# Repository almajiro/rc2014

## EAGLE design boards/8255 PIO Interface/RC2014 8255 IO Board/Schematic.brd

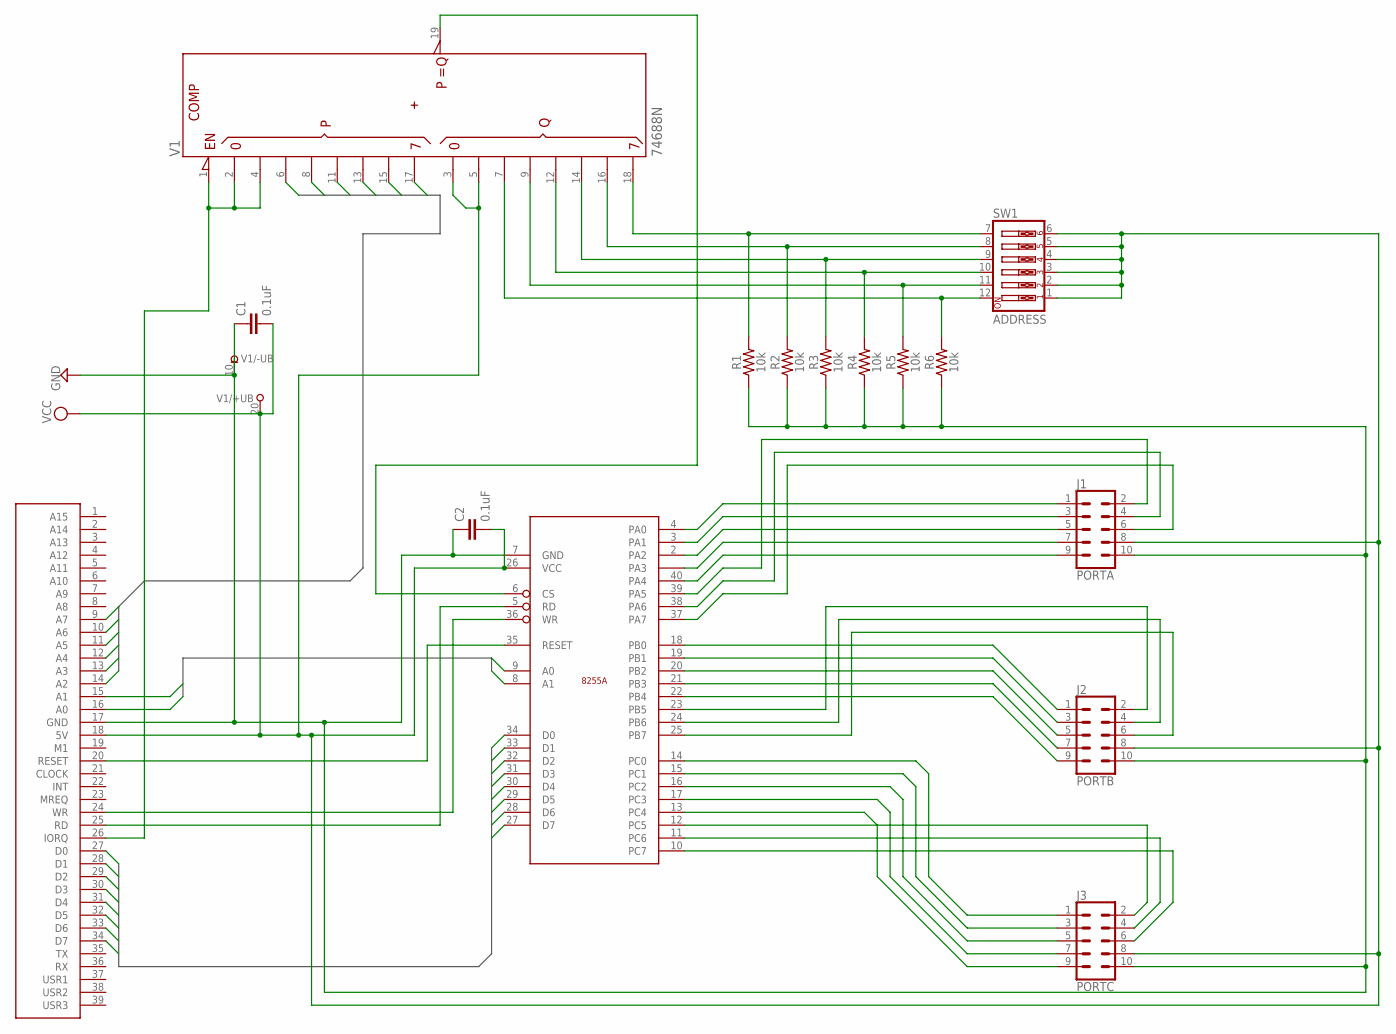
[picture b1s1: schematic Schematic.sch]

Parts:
C1, C2: 0.1uF; CAP-PTH-SMALL-KIT
J1: PORTA; 2X5-SHROUDED
J2: PORTB; 2X5-SHROUDED
J3: PORTC; 2X5-SHROUDED
R1, R2, R3, R4, R5, R6: 10k; AXIAL-0.3
SW1: ADDRESS; EDG-06
U$1: RC2014BUS
U$2: 8255
V1: 74688N; DIL20

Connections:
ADRBUS0: U$1.14 (A2), U$1.15 (A1), U$1.16 (A0), U$2.9 (A0), V1.6 (P2)
ADRBUS1: U$1.13 (A3), U$2.8 (A1), V1.8 (P3)
ADRBUS2: U$1.12 (A4), V1.11 (P4)
ADRBUS3: U$1.11 (A5), V1.13 (P5)
ADRBUS4: U$1.10 (A6), V1.15 (P6)
ADRBUS5: U$1.9 (A7), V1.17 (P7)
DATABUS0: U$1.27 (D0), U$2.34 (D0)
DATABUS1: U$1.28 (D1), U$2.33 (D1)
DATABUS2: U$1.29 (D2), U$2.32 (D2)
DATABUS3: U$1.30 (D3), U$2.31 (D3)
DATABUS4: U$1.31 (D4), U$2.30 (D4)
DATABUS5: U$1.32 (D5), U$2.29 (D5)
DATABUS6: U$1.33 (D6), U$2.28 (D6)
DATABUS7: U$1.34 (D7), U$2.27 (D7)
GND: C1.1, C2.1, J1.10, J2.10, J3.10, R1.P$1 (1), R2.P$1 (1), R3.P$1 (1), R4.P$1 (1), R5.P$1 (1), R6.P$1 (1), U$1.17 (GND), U$2.7 (GND), V1.10 (-UB)
unnamed: U$1.20 (RESET), U$2.35 (RESET)
unnamed: U$1.25 (RD), U$2.5 (RD)
unnamed: U$1.24 (WR), U$2.36 (WR)
unnamed: U$2.6 (CS), V1.19 (!P=Q)
unnamed: U$1.26 (IORQ), V1.1 (!G), V1.2 (P0), V1.4 (P1)
unnamed: R1.P$2 (2), SW1.7, V1.18 (Q7)
unnamed: R2.P$2 (2), SW1.8, V1.16 (Q6)
unnamed: R3.P$2 (2), SW1.9, V1.14 (Q5)
unnamed: R4.P$2 (2), SW1.10, V1.12 (Q4)
unnamed: R5.P$2 (2), SW1.11, V1.9 (Q3)
unnamed: R6.P$2 (2), SW1.12, V1.7 (Q2)
unnamed: J2.1, U$2.18 (PB0)
unnamed: J1.7, U$2.1 (PA3)
unnamed: J1.9, U$2.40 (PA4)
unnamed: J1.2, U$2.39 (PA5)
unnamed: J1.4, U$2.38 (PA6)
unnamed: J1.6, U$2.37 (PA7)
unnamed: J1.1, U$2.4 (PA0)
unnamed: J1.3, U$2.3 (PA1)
unnamed: J1.5, U$2.2 (PA2)
unnamed: J2.3, U$2.19 (PB1)
unnamed: J2.5, U$2.20 (PB2)
unnamed: J2.7, U$2.21 (PB3)
unnamed: J2.9, U$2.22 (PB4)
unnamed: J2.2, U$2.23 (PB5)
unnamed: J2.4, U$2.24 (PB6)
unnamed: J2.6, U$2.25 (PB7)
unnamed: J3.1, U$2.14 (PC0)
unnamed: J3.3, U$2.15 (PC1)
unnamed: J3.5, U$2.16 (PC2)
unnamed: J3.7, U$2.17 (PC3)
unnamed: J3.9, U$2.13 (PC4)
unnamed: J3.2, U$2.12 (PC5)
unnamed: J3.4, U$2.11 (PC6)
unnamed: J3.6, U$2.10 (PC7)
VCC: C1.2, C2.2, J1.8, J2.8, J3.8, SW1.1, SW1.2, SW1.3, SW1.4, SW1.5, SW1.6, U$1.18 (5V), U$2.26 (VCC), V1.3 (Q0), V1.5 (Q1), V1.20 (+UB)

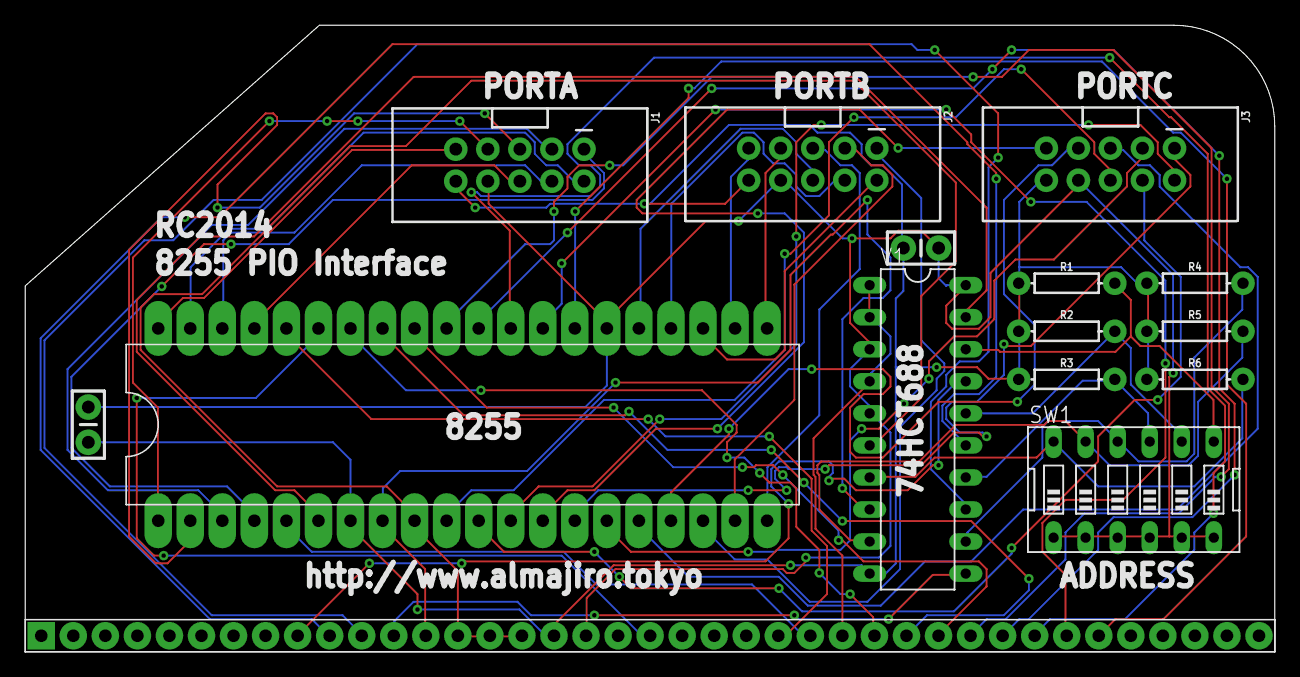
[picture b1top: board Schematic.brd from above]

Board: 2 copper layers, 99.0 x 49.7 mm, 15 parts (0 on the bottom side), 51 nets.

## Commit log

2017-12-31 add program5.3.asm
2017-12-31 add program5.4.asm
2017-12-31 add program5.7.asm
2017-12-31 add program5.9.asm
2017-12-31 add program5.10.asm
2018-01-01 add challenge/program1,2,3,4,5 .asm
2018-01-01 add challenge 6,7,8,9,10 asm source
2018-01-01 add challenge 14 asm
2018-01-01 add challenge 15 asm
2018-01-02 add challenge 17 asm
2018-01-02 add challenge 18 asm
2018-01-02 add challenge 19 asm
2018-01-05 add eagle projects
2018-01-07 add schematic
2018-01-12 add 16x2 LCD Project
2018-01-13 add program28.asm@
2018-01-20 add program23
2018-02-10 add challenge 24
2018-02-10 add challenge 29
2018-02-11 add challenge 30
2018-02-11 fix challenge 30
2018-02-12 add challenge 31
2018-02-17 add challenge 32
2018-02-17 add challenge 33

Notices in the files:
boards/8255 PIO Interface/RC2014 8255 IO Board/Schematic.brd:
(C) 2018 Kuroki Almajiro
parts and their libraries:
SparkFun-Connectors: Licensing: Creative Commons ShareAlike 4.0 International - https://creativecommons.org/licenses/by-sa/4.0
